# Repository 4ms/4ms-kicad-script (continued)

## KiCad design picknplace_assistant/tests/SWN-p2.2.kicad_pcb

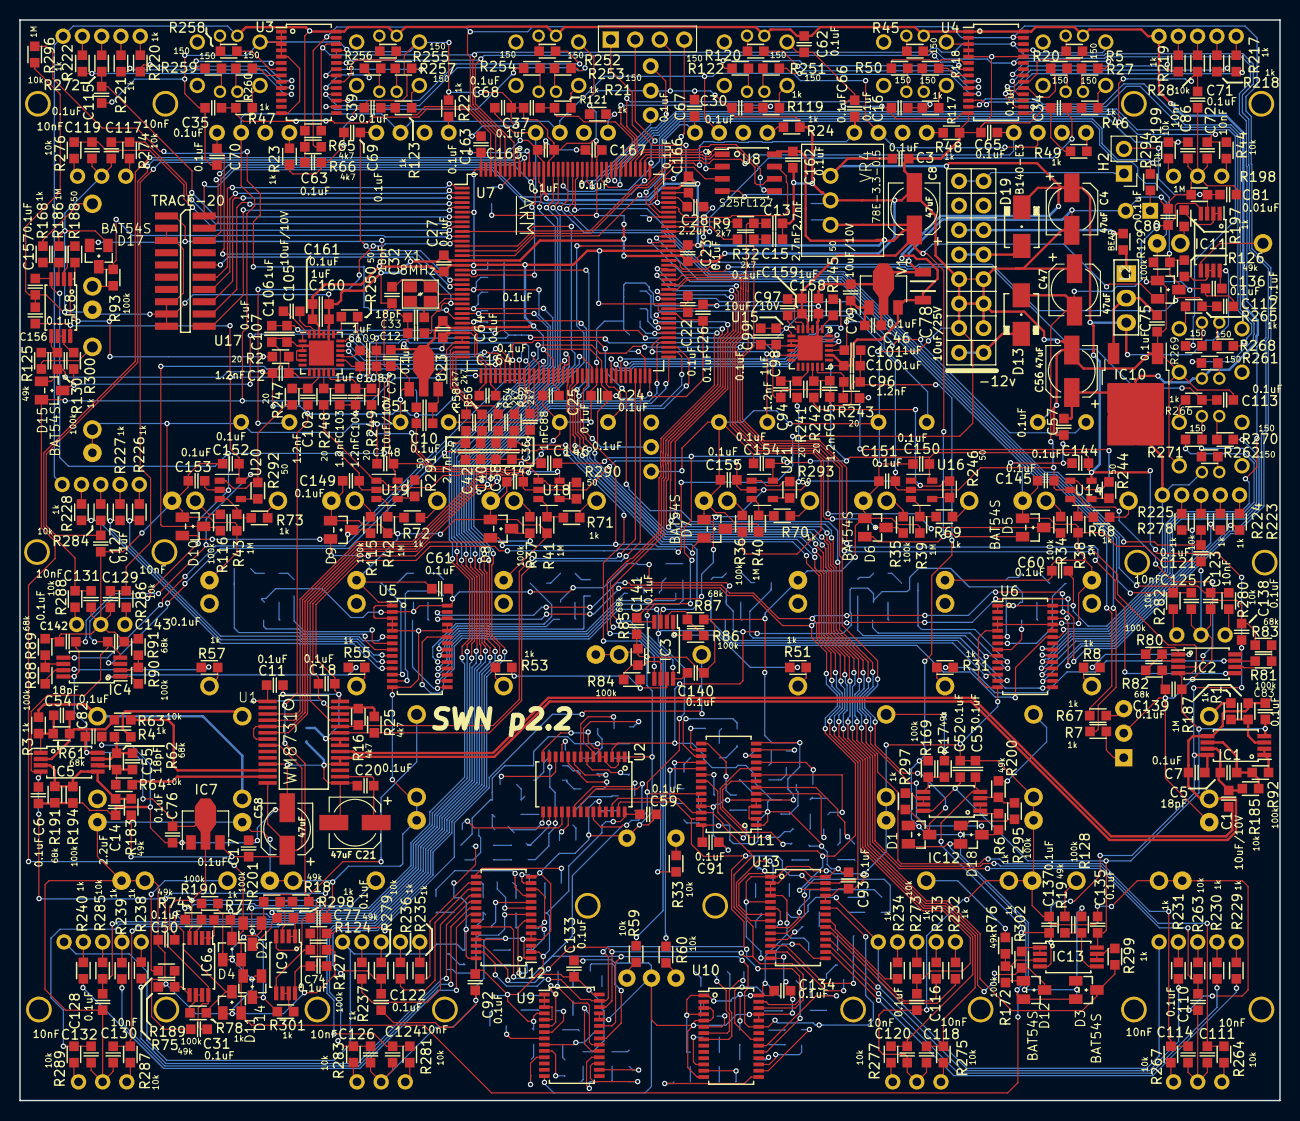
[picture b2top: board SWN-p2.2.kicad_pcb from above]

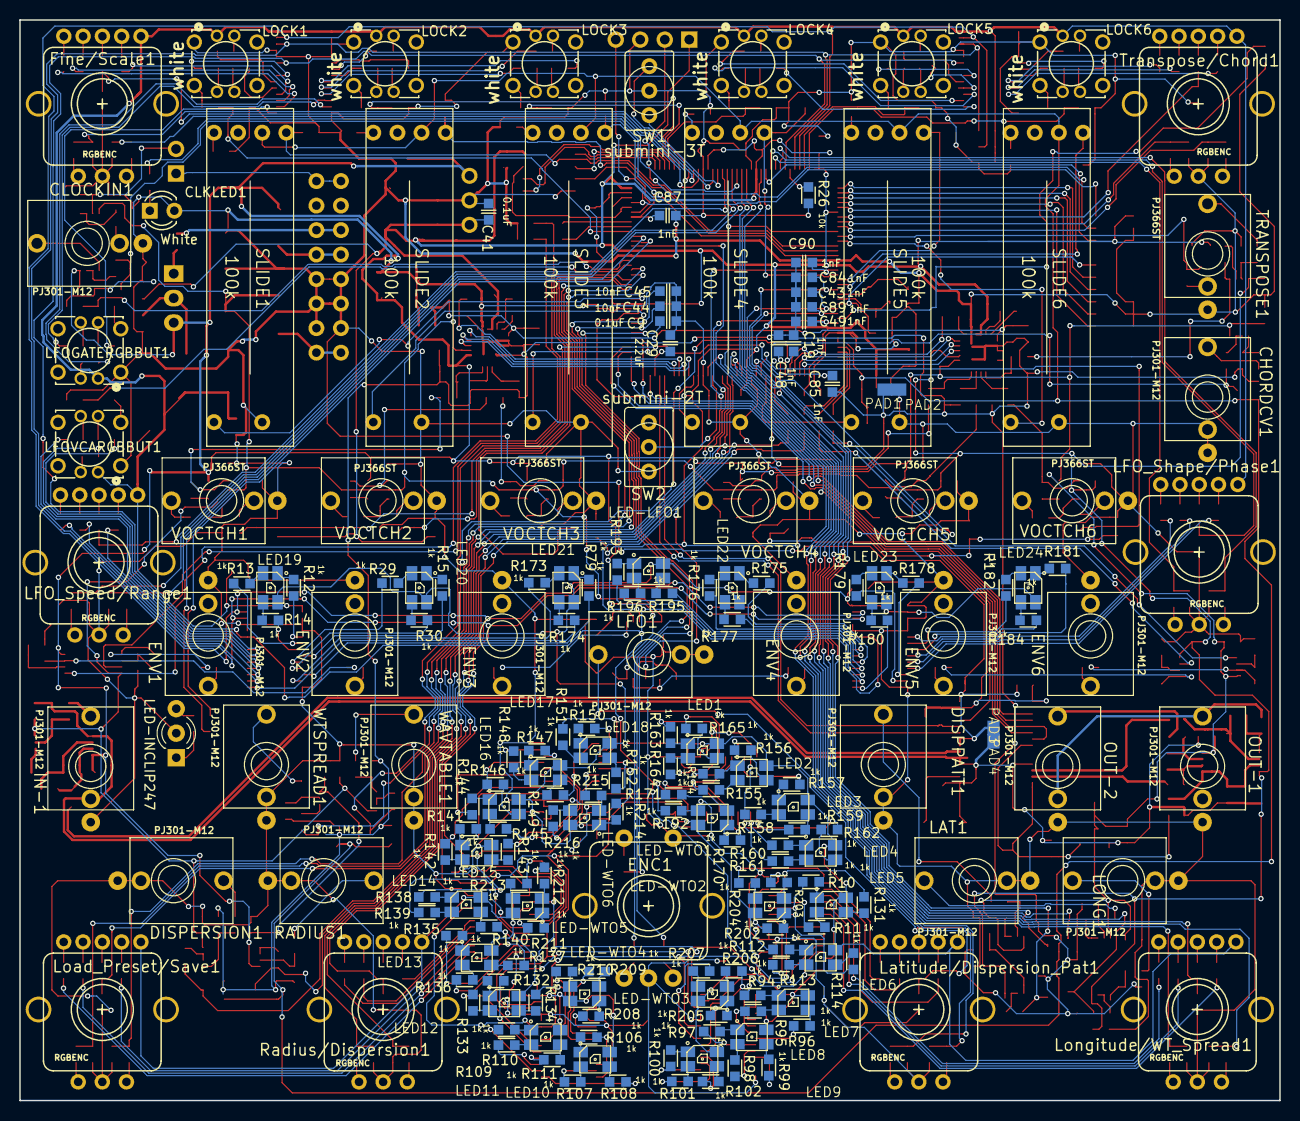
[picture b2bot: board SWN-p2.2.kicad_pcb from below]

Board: 2 copper layers, 130.6 x 112.0 mm, 614 parts (196 on the bottom side), 578 nets.

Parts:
C1, C51, C79, C97, C105: 10uF/10V; C0603
C2, C94, C95, C96, C102, C103, C104: 1.2nF; C0603
C3, C6, C7, C9, C10, C11, C12, C16, C17, C18, C20, C22, C23, C24, C25, C26, C27, C30, C31, C34, C35, C37, C39, C41, C46, C50, C52, C53, C57, C59, C60, C61, C62, C63, C64, C65, C66, C67, C68, C69, C70, C71, C73, C74, C75, C76, C77, C80, C82, C83, C91, C92, C93, C99, C107, C110, C112, C113, C115, C116, C121, C122, C127, C128, C133, C134, C135, C136, C137, C138, C139, C140, C141, C142, C143, C144, C145, C146, C147, C148, C149, C150, C151, C152, C153, C154, C155, C156, C157, C159, C161, C162, C163, C164, C165, C166, C167: 0.1uF; C0603
C4, C8, C21, C47, C56, C58: 47uF; CP_Elec_5x5.3
C5, C32, C33, C54, C55: 18pF; C0603
C13, C15, C36, C38, C40, C42: 2.7nF; C0603
C14, C28, C29: 2.2uF; C0603
C19, C43, C48, C49, C84, C85, C87, C88, C89, C90: 1nF; C0603
C44, C45, C72, C86, C111, C114, C117, C118, C119, C120, C123, C124, C125, C126, C129, C130, C131, C132: 10nF; C0603
C78: 10uF/25V; C1206
C81: 0.01uF; C0603
C98, C100, C101, C106, C108, C109, C158, C160: 1uF; C0603
CHORDCV1: PJ301-M12; PJ301M-12
CLKLED1: White; LED-C1-A2-3MM-VERT
CLOCKIN1: PJ301-M12; PJ301M-12
D1, D2, D3, D4, D5, D6, D7, D8, D9, D10, D11, D12, D14, D15, D16, D17, D18: BAT54S; SOT23
D13, D19: B140-E3; SMA_Standard
DISPERSION1: PJ301-M12; PJ301M-12
DISPPATT1: PJ301-M12; PJ301M-12
ENC1: ROTENC-BUTTON-A; ROTENC-12MM-BUT
ENV1, ENV2, ENV3, ENV4, ENV5, ENV6: PJ301-M12; PJ301M-12
Fine/Scale1: RGBENC; RGB_ROTARY_ENCODER
H1: TRACE-20; CONN-2x10-SMT-127
H2: BUSCLK; Pin_Header_Straight_1x02_Pitch2.54mm
IC1, IC5, IC8: NJM2068; TSSOP-8_4.4x3mm_Pitch0.65mm
IC2, IC3, IC4, IC6, IC9, IC11, IC12, IC13: TL082; TSSOP-8_4.4x3mm_Pitch0.65mm
IC7: MCP1703x-3302E/MB; SOT-89-3
IC10: LD1117ADT33TR; TO-252-2
IN-1: PJ301-M12; PJ301M-12
J1: HEADER-1X3-TH; Pin_Header_Straight_1x03
J2: HEADER-2X8-TH; HEADER-2X8-TH_eagle_pinout
L2: BEAD; R0603
LAT1: PJ301-M12; PJ301M-12
LED1, LED2, LED3, LED4, LED5, LED6, LED7, LED8, LED9, LED10, LED11, LED12, LED13, LED14, LED15, LED16, LED17, LED18, LED19, LED20, LED21, LED22, LED23, LED24: LED-RGB-CA-HEBEI; LED-PLCC4
LED-INCLIP247: LEDX2A; LED_D3.0mm-3
LED-LFO1: LED-RGB-CA-HEBEI; LED-PLCC4
LED-WTO1, LED-WTO2, LED-WTO3, LED-WTO4, LED-WTO5, LED-WTO6: LED-RGB-CA-HEBEI; LED-PLCC4
LFO1: PJ301-M12; PJ301M-12
LFOGATERGBBUT1: SPST-ILLUM-RGB; RGB-SPST-LED-TC002
LFOVCARGBBUT1: SPST-ILLUM-RGB; RGB-SPST-LED-TC002
LFO_Shape/Phase1: RGBENC; RGB_ROTARY_ENCODER
LFO_Speed/Range1: RGBENC; RGB_ROTARY_ENCODER
LOCK1, LOCK2, LOCK3, LOCK4, LOCK5, LOCK6: SPST-ILLUM-RGB; RGB-SPST-LED-TC002
LONG1: PJ301-M12; PJ301M-12
Latitude/Dispersion_Pat1: RGBENC; RGB_ROTARY_ENCODER
Load_Preset/Save1: RGBENC; RGB_ROTARY_ENCODER
Longitude/WT_Spread1: RGBENC; RGB_ROTARY_ENCODER
OUT-1, OUT-2: PJ301-M12; PJ301M-12
PAD1, PAD2, PAD3, PAD4: PAD-06
R1, R3, R4, R6, R7, R8, R10, R11, R12, R13, R14, R15, R21, R22, R23, R24, R29, R30, R31, R46, R47, R48, R49, R51, R53, R55, R57, R67, R68, R69, R70, R71, R72, R73, R77, R78, R79, R94, R95, R96, R97, R98, R99, R100, R101, R102, R106, R107, R108, R109, R110, R111, R112, R113, R114, R117, R119, R121, R123, R131, R132, R133, R134, R135, R136, R137, R138, R139, R140, R141, R142, R143, R144, R145, R146, R147, R148, R149, R150, R151, R152, R154, R155, R156, R157, R158, R159, R160, R161, R162, R163, R164, R165, R168, R170, R171, R173, R174, R175, R176, R177, R178, R179, R180, R181, R182, R184, R192, R193, R195, R196, R197, R202, R203, R204, R205, R206, R207, R208, R209, R210, R211, R212, R213, R214, R215, R216, R217, R218, R219, R220, R221, R222, R223, R224, R225, R226, R227, R228, R229, R230, R231, R232, R233, R234, R235, R236, R237, R238, R239, R240, R265, R266, R297, R298, R299, R300, R301, R302: 1k; R0603
R2, R241, R242, R243, R247, R248, R249: 20; R0603
R5, R20, R27, R45, R50, R118, R120, R122, R251, R252, R253, R254, R255, R256, R257, R258, R259, R260, R261, R262, R268, R269, R270, R271: 150; R0603
R9, R32, R52, R54, R56, R58: 2k7; R0603
R16, R25, R65, R66: 4k7; R0603
R17, R18, R19, R74, R75, R76, R124, R125, R126, R183, R200: 49k; R0603
R26, R28, R33, R44, R59, R60, R63, R64, R185, R199, R263, R264, R267, R272, R273, R274, R275, R276, R277, R278, R279, R280, R281, R282, R283, R284, R285, R286, R287, R288, R289, R294: 10k; R0603
R34, R35, R36, R37, R80, R81, R84, R86, R88, R90, R92, R93, R115, R116, R127, R128, R129, R130, R169, R172, R189, R190, R194, R201, R295: 100k; R0603
R38, R39, R40, R41, R42, R43, R186, R187, R198, R296: 1M; R0603
R61, R62, R82, R83, R85, R87, R89, R91, R191: 68k; R0603
R188, R244, R245, R246, R250, R290, R291, R292, R293: 50; R0603
RADIUS1: PJ301-M12; PJ301M-12
Radius/Dispersion1: RGBENC; RGB_ROTARY_ENCODER
SLIDE1, SLIDE2, SLIDE3, SLIDE4, SLIDE5, SLIDE6: 100k; POT-SLIDER-LED-ALPHA-RA2045F-20
SW1: submini-3T; SPDT-SUB
SW2: submini-2T; SPDT-SUB
SWD_1: HEADER-1X4; Pin_Header_Straight_1x04_Pitch2.54mm
TRANSPOSE1: PJ366ST; PJ301M-12
Transpose/Chord1: RGBENC; RGB_ROTARY_ENCODER
U1: WM8731; SSOP-28
U2, U3, U4, U5, U6, U9, U10, U11, U12, U13: PCA9685; TSSOP-28_4.4x9.7mm_Pitch0.65mm
U7: STM32F427ZG; LQFP-144_ARM_20x20mm_Pitch0.5mm
U8: S25FL127; SOIC-8_3.9x4.9mm_Pitch1.27mm
U14, U16, U18, U19, U20, U21: LM7321; SOT-23-5
U15, U17: ADS8634; QFN-24-1EP_4x4mm_Pitch0.5mm
U23: MCP1703x-3302E/MB; SOT-89-3
V1: KA78L05; SOT-89-3
VOCTCH1, VOCTCH2, VOCTCH3, VOCTCH4, VOCTCH5, VOCTCH6: PJ366ST; PJ301M-12
VR4: 78E-3.3-0.5; RECOM-DCDC
WAVTABLE1: PJ301-M12; PJ301M-12
WTSPREAD1: PJ301-M12; PJ301M-12
X1: 8MHz; FA-238-Pins1and2diag

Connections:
5VEXT: J1.1, L2.2
+3.3V: C8.1, C11.1, C18.1, C22.1, C23.1, C24.1, C25.1, C26.1, C27.1, C41.1, C64.1, C73.1, C158.1, C159.1, C160.1, C161.1, C162.1, C163.1, C164.1, C165.1, C166.1, C167.1, D5.2, D6.2, D7.2, D8.2, D9.2, D10.2, D16.2, D17.2, H1.1, R16.1, R25.1, SWD_1.1, U1.1, U1.27, U7.6, U7.17, U7.30, U7.39, U7.52, U7.62, U7.72, U7.82, U7.84, U7.95, U7.108, U7.121, U7.131, U7.143, U7.144, U8.8, U15.21, U15.22, U17.21, U17.22, U23.2, VR4.3
+5V: C46.2, C79.2, C98.1, C99.1, C106.1, C107.1, U15.1, U17.1, V1.1
+12V: C3.1, C4.1, C7.2, C50.2, C53.2, C76.1, C77.2, C78.1, C82.2, C100.1, C108.1, C136.2, C137.2, C138.2, C140.2, C142.2, C144.1, C146.1, C148.1, C150.1, C152.1, C154.1, C156.1, D19.1, IC1.8, IC2.8, IC3.8, IC4.8, IC5.8, IC6.4, IC7.2, IC8.8, IC9.4, IC11.8, IC12.4, IC13.4, J1.3, U14.5, U15.14, U16.5, U17.14, U18.5, U19.5, U20.5, U21.5, V1.3, VR4.1
-12V: C6.1, C31.1, C47.2, C52.1, C74.1, C80.1, C83.1, C101.1, C109.1, C135.1, C139.2, C141.2, C143.2, C145.1, C147.1, C149.1, C151.1, C153.1, C155.1, C157.1, D13.2, IC1.4, IC2.4, IC3.4, IC4.4, IC5.4, IC6.8, IC8.4, IC9.8, IC11.4, IC12.8, IC13.8, U14.2, U15.15, U16.2, U17.15, U18.2, U19.2, U20.2, U21.2
/V/OCT ADC/TRANSPOSEADC: IC8.1, R2.1, R188.1
/V/OCT ADC/VOLTADC1: R243.1, R244.1, U14.1
/V/OCT ADC/VOLTADC2: R242.1, R246.1, U16.1
/V/OCT ADC/VOLTADC3: R241.1, R293.1, U21.1
/V/OCT ADC/VOLTADC4: R249.1, R290.1, U18.1
/V/OCT ADC/VOLTADC5: R248.1, R291.1, U19.1
/V/OCT ADC/VOLTADC6: R247.1, R292.1, U20.1
ADC-VDD: C10.1, C51.1, D1.2, D2.2, D3.2, D4.2, D11.2, D12.2, D14.2, D15.2, D18.2, SLIDE1.P1, SLIDE2.P1, SLIDE3.P1, SLIDE4.P1, SLIDE5.P1, SLIDE6.P1, U7.32, U7.33, U23.3
AGND: C6.2, C7.1, C14.2, C17.2, C20.2, C21.2, C58.2, C76.2, C82.1, C83.2, IC1.5, IC7.1, IN-1.3, PAD3.1, R187.2, R191.1, R194.1, U1.11, U1.15, U1.18, U1.19
CHORDADC: C88.1, D15.3, R300.2, U7.47
CLKINADC: C87.1, D16.3, R126.2, R129.1, U7.102
CLKLED: R294.1, U7.127
CODEC-VDD: C17.1, C58.1, IC7.3, R183.2, U1.8, U1.14
DISPADC: C90.1, D3.3, R299.2, U7.18
DISPPATADC: C84.1, D2.3, R298.2, U7.22
ENVPWM1: R9.2, U7.101
ENVPWM2: R32.2, U7.100
ENVPWM3: R52.2, U7.46
ENVPWM4: R54.2, U7.36
ENVPWM5: R56.2, U7.35
ENVPWM6: R58.2, U7.34
FINEENC1: C72.1, R44.2, U7.118
FINEENC2: C86.1, R199.1, U7.119
FINESW1: C71.1, R28.2, U7.117
GND: C3.2, C4.2, C8.2, C9.2, C11.2, C12.2, C13.2, C15.2, C16.2, C18.2, C22.2, C23.2, C24.2, C25.2, C26.2, C27.2, C28.2, C29.2, C30.2, C31.2, C32.1, C33.1, C34.2, C35.2, C36.2, C37.2, C38.2, C39.2, C40.2, C41.2, C42.2, C44.2, C45.2, C46.1, C47.1, C50.1, C52.2, C53.1, C56.2, C57.2, C59.2, C60.2, C61.2, C62.2, C63.2, C64.2, C65.2, C66.2, C67.2, C68.2, C69.2, C70.2, C71.2, C72.2, C73.2, C74.2, C75.2, C77.1, C78.2, C79.1, C80.2, C81.2, C86.2, C87.2, C91.2, C92.2, C93.2, C110.2, C111.2, C112.2, C113.2, C114.2, C115.2, C116.2, C117.2, C118.2, C119.2, C120.2, C121.2, C122.2, C123.2, C124.2, C125.2, C126.2, C127.2, C128.2, C129.2, C130.2, C131.2, C132.2, C133.2, C134.2, C135.2, C136.1, C137.1, C138.1, C139.1, C140.1, C141.1, C142.1, C143.1, C144.2, C145.2, C146.2, C147.2, C148.2, C149.2, C150.2, C151.2, C152.2, C153.2, C154.2, C155.2, C156.2, C157.2, C158.2, C159.2, C160.2, C161.2, C162.2, C163.2, C164.2, C165.2, C166.2, C167.2, CHORDCV1.2, CHORDCV1.3, CLKLED1.1, CLOCKIN1.2, D5.1, D6.1, D7.1, D8.1, D9.1, D10.1, D16.1, D17.1, DISPERSION1.2, DISPERSION1.3, DISPPATT1.2, DISPPATT1.3, ENC1.2, ENC1.SW2, ENV1.2, ENV2.2, ENV3.2, ENV4.2, ENV5.2, ENV6.2, Fine/Scale1.2, H1.3, H1.5, H1.15, H1.17, H1.19, IC10.1, IN-1.2, J2.3, J2.4, J2.5, J2.6, J2.7, J2.8, LAT1.2, LAT1.3, LED-INCLIP247.2, LFO1.2, LFO1.3, LFOGATERGBBUT1.1, LFOVCARGBBUT1.1, LFO_Shape/Phase1.2, LFO_Speed/Range1.2, LOCK1.1, LOCK2.1, LOCK3.1, LOCK4.1, LOCK5.1, LOCK6.1, LONG1.2, LONG1.3, Latitude/Dispersion_Pat1.2, Load_Preset/Save1.2, Longitude/WT_Spread1.2, OUT-1.2, OUT-2.2, PAD2.1, PAD4.1, R21.2, R22.2, R23.2, R24.2, R26.2, R38.2, R39.2, R40.2, R41.2, R42.2, R43.2, R48.2, R49.2, R82.2, R83.2, R85.2, R87.2, R89.2, R91.2, R129.2, R186.2, R198.2, R296.1, RADIUS1.2, RADIUS1.3, Radius/Dispersion1.2, SLIDE1.P3, SLIDE2.P3, SLIDE3.P3, SLIDE4.P3, SLIDE5.P3, SLIDE6.P3, SW1.2, SW2.1, SWD_1.3, TRANSPOSE1.2, Transpose/Chord1.2, U1.21, U1.22, U1.28, U2.1, U2.2, U2.4, U2.5, U2.14, U2.24, U2.25, U3.1, U3.2, U3.3, U3.4, U3.5, U3.14, U3.24, U3.25, U4.2, U4.3, U4.4, U4.5, U4.14, U4.24, U4.25, U5.1, U5.3, U5.4, U5.5, U5.14, U5.24, U5.25, U6.3, U6.4, U6.5, U6.14, U6.24, U6.25, U7.16, U7.31, U7.38, U7.51, U7.61, U7.83, U7.94, U7.107, U7.120, U7.130, U8.4, U9.14, U9.24, U9.25, U10.2, U10.3, U10.5, U10.14, U10.24, U10.25, U11.2, U11.4, U11.5, U11.14, U11.24, U11.25, U12.1, U12.4, U12.5, U12.14, U12.24, U12.25, U13.1, U13.5, U13.14, U13.24, U13.25, U15.20, U17.20, U23.1, V1.2, VOCTCH1.2, VOCTCH2.2, VOCTCH3.2, VOCTCH4.2, VOCTCH5.2, VOCTCH6.2, VR4.2, WAVTABLE1.2, WAVTABLE1.3, WTSPREAD1.2, WTSPREAD1.3
GNDADC: C2.2, C10.2, C19.2, C43.2, C48.2, C49.2, C51.2, C84.2, C85.2, C88.2, C89.2, C90.2, C94.2, C95.2, C96.2, C98.2, C99.2, C100.2, C101.2, C102.2, C103.2, C104.2, C106.2, C107.2, C108.2, C109.2, D1.1, D2.1, D3.1, D4.1, D11.1, D12.1, D14.1, D15.1, D18.1, PAD1.1, R127.2, R128.2, R130.2, R169.2, R172.2, R189.2, R190.2, R201.2, R295.2, U15.2, U15.3, U15.5, U15.25, U17.2, U17.3, U17.5, U17.25
I2C1_SCL: R65.2, U2.26, U3.26, U4.26, U5.26, U6.26, U7.139, U9.26, U10.26, U11.26, U12.26, U13.26
I2C1_SDA: R66.2, U2.27, U3.27, U4.27, U5.27, U6.27, U7.140, U9.27, U10.27, U11.27, U12.27, U13.27
I2C2_SCL: R16.2, U1.24, U7.69
I2C2_SDA: R25.2, U1.23, U7.70
I2S2_LRCK: U1.5, U1.7, U7.73
I2S2_MCLK: U1.25, U7.96
I2S2_SCLK: U1.3, U7.74
I2S2_SDI: U1.6, U7.75
I2S2_SDO: U1.4, U7.76
IN-CLIP-L: R7.2, U7.98
IN-CLIP-R: R67.1, U7.97
IN-L: C1.1, U1.20
KEYS: SW1.1, U7.123
LATADC: C43.1, D4.3, R77.2, U7.26
LATITUDEENC1: C124.1, R281.2, U7.53
LATITUDEENC2: C126.1, R283.1, U7.54
LATITUDESW1: C122.1, R279.2, U7.10
LEDRING_OE: U2.23, U3.23, U4.23, U5.23, U6.23, U7.137, U9.23, U10.23, U11.23, U12.23, U13.23
LEDRING_VCC: C56.1, C57.1, C59.1, C60.1, C61.1, C62.1, C63.1, C91.1, C92.1, C93.1, C133.1, C134.1, Fine/Scale1.8, IC10.2, LED1.2, LED2.2, LED3.2, LED4.2, LED5.2, LED6.2, LED7.2, LED8.2, LED9.2, LED10.2, LED11.2, LED12.2, LED13.2, LED14.2, LED15.2, LED16.2, LED17.2, LED18.2, LED19.2, LED20.2, LED21.2, LED22.2, LED23.2, LED24.2, LED-LFO1.2, LED-WTO1.2, LED-WTO2.2, LED-WTO3.2, LED-WTO4.2, LED-WTO5.2, LED-WTO6.2, LFOGATERGBBUT1.5, LFOVCARGBBUT1.5, LFO_Shape/Phase1.8, LFO_Speed/Range1.8, LOCK1.5, LOCK2.5, LOCK3.5, LOCK4.5, LOCK5.5, LOCK6.5, Latitude/Dispersion_Pat1.8, Load_Preset/Save1.8, Longitude/WT_Spread1.8, R65.1, R66.1, Radius/Dispersion1.8, Transpose/Chord1.8, U2.3, U2.28, U3.28, U4.1, U4.28, U5.2, U5.28, U6.1, U6.2, U6.28, U9.4, U9.28, U10.1, U10.4, U10.28, U11.1, U11.3, U11.28, U12.2, U12.3, U12.28, U13.2, U13.3, U13.4, U13.28
LFOADC: C89.1, D14.3, R301.2, U7.27
LFOGATEBUT: C112.1, R265.1, U7.93
LFOGATE_B: R269.1, U4.15
LFOGATE_G: R261.2, U4.13
LFOGATE_R: R268.1, U4.12
LFOSHAPEENC1: C129.1, R286.2, U7.135
LFOSHAPEENC2: C131.1, R288.1, U7.136
LFOSHAPESW1: C127.1, R284.2, U7.134
LFOSPEEDENC1: C123.1, R280.2, U7.125
LFOSPEEDENC2: C125.1, R282.1, U7.126
LFOSPEEDSW1: C121.1, R278.2, U7.124
LFOVCABUT: C113.1, R266.1, U7.92
LFOVCA_B: R271.1, U6.21
LFOVCA_G: R262.2, U6.20
LFOVCA_R: R270.1, U6.19
LOCK1_B: R27.1, U4.21
LOCK1_G: R5.2, U4.20
LOCK1_R: R20.1, U4.19
LOCK2_B: R118.1, U4.8
LOCK2_G: R45.2, U4.7
LOCK2_R: R50.1, U4.6
LOCK3_B: R251.1, U4.11
LOCK3_G: R120.2, U4.10
LOCK3_R: R122.1, U4.9
LOCK4_B: R254.1, U3.18
LOCK4_G: R252.2, U3.17
LOCK4_R: R253.1, U3.16
LOCK5_B: R257.1, U3.21
LOCK5_G: R255.2, U3.20
LOCK5_R: R256.1, U3.19
LOCK6_B: R260.1, U3.8
LOCK6_G: R258.2, U3.7
LOCK6_R: R259.1, U3.6
LOCKBUT1: C34.1, R46.1, U7.99
LOCKBUT2: C16.1, R117.1, U7.114
LOCKBUT3: C30.1, R119.1, U7.115
LOCKBUT4: C37.1, R121.1, U7.116
LOCKBUT5: C39.1, R123.1, U7.141
LOCKBUT6: C35.1, R47.1, U7.142
LONGADC: C48.1, D11.3, R78.2, U7.45
LONGITUDEENC1: C130.1, R287.2, U7.128
LONGITUDEENC2: C132.1, R289.1, U7.129
LONGITUDESW1: C128.1, R285.2, U7.132
MUTES: SW1.3, U7.122
NRST: C12.1, H1.10, U7.25
unnamed: C1.2, C5.1, IC1.7, R185.2
unnamed: C2.1, R2.2, U17.8
unnamed: C5.2, IC1.6, R92.2, R185.1
unnamed: C13.1, IC2.3, R9.1
unnamed: C14.1, IC5.3, IC5.5, R183.1, R191.2, R194.2
unnamed: C15.1, IC2.5, R32.1
unnamed: C20.1, C21.1, U1.16
unnamed: C28.1, U7.106
unnamed: C29.1, U7.71
unnamed: C32.2, U7.23, X1.1
unnamed: C33.2, U7.24, X1.2
unnamed: C36.1, IC3.3, R52.1
unnamed: C38.1, IC3.5, R54.1
unnamed: C40.1, IC4.3, R56.1
unnamed: C42.1, IC4.5, R58.1
unnamed: C54.1, IC5.1, R3.2, R61.2
unnamed: C54.2, IC5.2, R61.1, R63.2
unnamed: C55.1, IC5.7, R4.2, R62.2
unnamed: C55.2, IC5.6, R62.1, R64.2
unnamed: C75.1, IC10.3, J1.2
unnamed: C94.1, R241.2, U15.9
unnamed: C95.1, R242.2, U15.10
unnamed: C96.1, R243.2, U15.11
unnamed: C97.1, U15.24
unnamed: C97.2, U15.23
unnamed: C102.1, R247.2, U17.9
unnamed: C103.1, R248.2, U17.10
unnamed: C104.1, R249.2, U17.11
unnamed: C105.1, U17.24
unnamed: C105.2, U17.23
unnamed: CHORDCV1.1, R125.1
unnamed: CLKLED1.2, R294.2
unnamed: CLOCKIN1.1, IC11.5
unnamed: CLOCKIN1.3, R197.1
unnamed: D13.1, J2.1, J2.2
unnamed: D19.2, J2.9, J2.10
unnamed: DISPERSION1.1, R19.1
unnamed: DISPPATT1.1, R18.1
unnamed: ENC1.1, R60.2
unnamed: ENC1.3, R59.1
unnamed: ENC1.SW1, R33.1
unnamed: ENV1.1, R8.1
unnamed: ENV2.1, R31.1
unnamed: ENV3.1, R51.1
unnamed: ENV4.1, R53.1
unnamed: ENV5.1, R55.1
unnamed: ENV6.1, R57.1
unnamed: Fine/Scale1.1, R44.1
unnamed: Fine/Scale1.3, R199.2
unnamed: Fine/Scale1.4, R217.2
unnamed: Fine/Scale1.5, R218.2
unnamed: Fine/Scale1.6, R28.1
unnamed: Fine/Scale1.7, R219.2
unnamed: H2.1, J2.15, J2.16
unnamed: IC1.1, IC1.2, R92.1
unnamed: IC1.3, R1.2, R187.1
unnamed: IC2.1, R8.2, R80.1
unnamed: IC2.2, R80.2, R82.1
unnamed: IC2.6, R81.2, R83.1
unnamed: IC2.7, R31.2, R81.1
unnamed: IC3.1, R51.2, R86.1
unnamed: IC3.2, R86.2, R87.1
unnamed: IC3.6, R84.2, R85.1
unnamed: IC3.7, R53.2, R84.1
unnamed: IC4.1, R55.2, R90.1
unnamed: IC4.2, R90.2, R91.1
unnamed: IC4.6, R88.2, R89.1
unnamed: IC4.7, R57.2, R88.1
unnamed: IC6.1, IC6.2, R77.1
unnamed: IC6.3, R74.2, R190.1
unnamed: IC6.5, R75.2, R189.1
unnamed: IC6.6, IC6.7, R78.1
unnamed: IC8.2, R188.2
unnamed: IC8.3, R168.1, R186.1
unnamed: IC8.5, R125.2, R130.1
unnamed: IC8.6, IC8.7, R300.1
unnamed: IC9.1, IC9.2, R298.1
unnamed: IC9.3, R18.2, R201.1
unnamed: IC9.5, R124.2, R127.1
unnamed: IC9.6, IC9.7, R301.1
unnamed: IC11.1, IC11.2, R197.2
unnamed: IC11.6, IC11.7, R126.1
unnamed: IC12.1, IC12.2, R6.1
unnamed: IC12.3, R200.2, R295.1
unnamed: IC12.5, R17.2, R169.1
unnamed: IC12.6, IC12.7, R297.1
unnamed: IC13.1, IC13.2, R302.1
unnamed: IC13.3, R76.2, R172.1
unnamed: IC13.5, R19.2, R128.1
unnamed: IC13.6, IC13.7, R299.1
unnamed: IN-1.1, R1.1
unnamed: J2.11, J2.12, L2.1
unnamed: LAT1.1, R74.1
unnamed: LED1.1, R163.2
unnamed: LED1.3, R165.2
unnamed: LED1.4, R164.2
unnamed: LED2.1, R154.2
unnamed: LED2.3, R156.2
unnamed: LED2.4, R155.2
unnamed: LED3.1, R157.2
unnamed: LED3.3, R159.2
unnamed: LED3.4, R158.2
unnamed: LED4.1, R160.2
unnamed: LED4.3, R162.2
unnamed: LED4.4, R161.2
unnamed: LED5.1, R10.2
unnamed: LED5.3, R131.2
unnamed: LED5.4, R11.2
unnamed: LED6.1, R112.2
unnamed: LED6.3, R114.2
unnamed: LED6.4, R113.2
unnamed: LED7.1, R94.2
unnamed: LED7.3, R96.2
unnamed: LED7.4, R95.2
unnamed: LED8.1, R97.2
unnamed: LED8.3, R99.2
unnamed: LED8.4, R98.2
unnamed: LED9.1, R100.2
unnamed: LED9.3, R102.2
unnamed: LED9.4, R101.2
unnamed: LED10.1, R106.2
unnamed: LED10.3, R108.2
unnamed: LED10.4, R107.2
unnamed: LED11.1, R109.2
unnamed: LED11.3, R111.2
unnamed: LED11.4, R110.2
unnamed: LED12.1, R132.2
unnamed: LED12.3, R134.2
unnamed: LED12.4, R133.2
unnamed: LED13.1, R135.2
unnamed: LED13.3, R137.2
unnamed: LED13.4, R136.2
unnamed: LED14.1, R138.2
unnamed: LED14.3, R140.2
unnamed: LED14.4, R139.2
unnamed: LED15.1, R141.2
unnamed: LED15.3, R143.2
unnamed: LED15.4, R142.2
unnamed: LED16.1, R144.2
unnamed: LED16.3, R146.2
unnamed: LED16.4, R145.2
unnamed: LED17.1, R147.2
unnamed: LED17.3, R149.2
unnamed: LED17.4, R148.2
unnamed: LED18.1, R150.2
unnamed: LED18.3, R152.2
unnamed: LED18.4, R151.2
unnamed: LED19.1, R12.2
unnamed: LED19.3, R14.2
unnamed: LED19.4, R13.2
unnamed: LED20.1, R15.2
unnamed: LED20.3, R30.2
unnamed: LED20.4, R29.2
unnamed: LED21.1, R79.2
unnamed: LED21.3, R174.2
unnamed: LED21.4, R173.2
unnamed: LED22.1, R175.2
unnamed: LED22.3, R177.2
unnamed: LED22.4, R176.2
unnamed: LED23.1, R178.2
unnamed: LED23.3, R180.2
unnamed: LED23.4, R179.2
unnamed: LED24.1, R181.2
unnamed: LED24.3, R184.2
unnamed: LED24.4, R182.2
unnamed: LED-INCLIP247.1, R7.1
unnamed: LED-INCLIP247.3, R67.2
unnamed: LED-LFO1.1, R193.2
unnamed: LED-LFO1.3, R196.2
unnamed: LED-LFO1.4, R195.2
unnamed: LED-WTO1.1, R170.2
unnamed: LED-WTO1.3, R192.2
unnamed: LED-WTO1.4, R171.2
unnamed: LED-WTO2.1, R202.2
unnamed: LED-WTO2.3, R204.2
unnamed: LED-WTO2.4, R203.2
unnamed: LED-WTO3.1, R205.2
unnamed: LED-WTO3.3, R207.2
unnamed: LED-WTO3.4, R206.2
unnamed: LED-WTO4.1, R208.2
unnamed: LED-WTO4.3, R210.2
unnamed: LED-WTO4.4, R209.2
unnamed: LED-WTO5.1, R211.2
unnamed: LED-WTO5.3, R213.2
unnamed: LED-WTO5.4, R212.2
unnamed: LED-WTO6.1, R214.2
unnamed: LED-WTO6.3, R216.2
unnamed: LED-WTO6.4, R215.2
unnamed: LFO1.1, R124.1
unnamed: LFOGATERGBBUT1.3, R265.2
unnamed: LFOGATERGBBUT1.6, R261.1
unnamed: LFOGATERGBBUT1.7, R268.2
unnamed: LFOGATERGBBUT1.8, R269.2
unnamed: LFOVCARGBBUT1.3, R266.2
unnamed: LFOVCARGBBUT1.6, R262.1
unnamed: LFOVCARGBBUT1.7, R270.2
unnamed: LFOVCARGBBUT1.8, R271.2
unnamed: LFO_Shape/Phase1.1, R286.1
unnamed: LFO_Shape/Phase1.3, R288.2
unnamed: LFO_Shape/Phase1.4, R226.2
unnamed: LFO_Shape/Phase1.5, R227.2
unnamed: LFO_Shape/Phase1.6, R284.1
unnamed: LFO_Shape/Phase1.7, R228.2
unnamed: LFO_Speed/Range1.1, R280.1
unnamed: LFO_Speed/Range1.3, R282.2
unnamed: LFO_Speed/Range1.4, R223.2
unnamed: LFO_Speed/Range1.5, R224.2
unnamed: LFO_Speed/Range1.6, R278.1
unnamed: LFO_Speed/Range1.7, R225.2
unnamed: LOCK1.3, R46.2
unnamed: LOCK1.6, R5.1
unnamed: LOCK1.7, R20.2
unnamed: LOCK1.8, R27.2
unnamed: LOCK2.3, R117.2
unnamed: LOCK2.6, R45.1
unnamed: LOCK2.7, R50.2
unnamed: LOCK2.8, R118.2
unnamed: LOCK3.3, R119.2
unnamed: LOCK3.6, R120.1
unnamed: LOCK3.7, R122.2
unnamed: LOCK3.8, R251.2
unnamed: LOCK4.3, R121.2
unnamed: LOCK4.6, R252.1
unnamed: LOCK4.7, R253.2
unnamed: LOCK4.8, R254.2
unnamed: LOCK5.3, R123.2
unnamed: LOCK5.6, R255.1
unnamed: LOCK5.7, R256.2
unnamed: LOCK5.8, R257.2
unnamed: LOCK6.3, R47.2
unnamed: LOCK6.6, R258.1
unnamed: LOCK6.7, R259.2
unnamed: LOCK6.8, R260.2
unnamed: LONG1.1, R75.1
unnamed: Latitude/Dispersion_Pat1.1, R281.1
unnamed: Latitude/Dispersion_Pat1.3, R283.2
unnamed: Latitude/Dispersion_Pat1.4, R235.2
unnamed: Latitude/Dispersion_Pat1.5, R236.2
unnamed: Latitude/Dispersion_Pat1.6, R279.1
unnamed: Latitude/Dispersion_Pat1.7, R237.2
unnamed: Load_Preset/Save1.1, R264.1
unnamed: Load_Preset/Save1.3, R267.2
unnamed: Load_Preset/Save1.4, R229.2
unnamed: Load_Preset/Save1.5, R230.2
unnamed: Load_Preset/Save1.6, R263.1
unnamed: Load_Preset/Save1.7, R231.2
unnamed: Longitude/WT_Spread1.1, R287.1
unnamed: Longitude/WT_Spread1.3, R289.2
unnamed: Longitude/WT_Spread1.4, R238.2
unnamed: Longitude/WT_Spread1.5, R239.2
unnamed: Longitude/WT_Spread1.6, R285.1
unnamed: Longitude/WT_Spread1.7, R240.2
unnamed: OUT-1.1, OUT-2.3, R3.1
unnamed: OUT-2.1, R4.1
unnamed: R10.1, U12.9
unnamed: R11.1, U12.10
unnamed: R12.1, U6.6
unnamed: R13.1, U6.7
unnamed: R14.1, U6.8
unnamed: R15.1, U6.9
unnamed: R17.1, WAVTABLE1.1
unnamed: R21.1, SLIDE4.LEDC
unnamed: R22.1, SLIDE5.LEDC
unnamed: R23.1, SLIDE6.LEDC
unnamed: R24.1, SLIDE3.LEDC
unnamed: R26.1, U7.138
unnamed: R29.1, U6.10
unnamed: R30.1, U6.11
unnamed: R34.2, VOCTCH1.3
unnamed: R35.1, VOCTCH2.3
unnamed: R36.1, VOCTCH3.3
unnamed: R37.2, VOCTCH4.3
unnamed: R38.1, R68.1, U14.3
unnamed: R39.1, R69.1, U16.3
unnamed: R40.1, R70.1, U21.3
unnamed: R41.1, R71.1, U18.3
unnamed: R42.1, R72.1, U19.3
unnamed: R43.1, R73.1, U20.3
unnamed: R48.1, SLIDE2.LEDC
unnamed: R49.1, SLIDE1.LEDC
unnamed: R68.2, VOCTCH1.1
unnamed: R69.2, VOCTCH2.1
unnamed: R70.2, VOCTCH3.1
unnamed: R71.2, VOCTCH4.1
unnamed: R72.2, VOCTCH5.1
unnamed: R73.2, VOCTCH6.1
unnamed: R76.1, RADIUS1.1
unnamed: R79.1, U6.12
unnamed: R93.2, TRANSPOSE1.3
unnamed: R94.1, U9.6
unnamed: R95.1, U9.7
unnamed: R96.1, U9.8
unnamed: R97.1, U9.9
unnamed: R98.1, U9.10
unnamed: R99.1, U9.11
unnamed: R100.1, U9.16
unnamed: R101.1, U9.17
unnamed: R102.1, U9.18
unnamed: R106.1, U10.12
unnamed: R107.1, U10.13
unnamed: R108.1, U10.15
unnamed: R109.1, U10.16
unnamed: R110.1, U10.17
unnamed: R111.1, U10.18
unnamed: R112.1, U12.6
unnamed: R113.1, U12.7
unnamed: R114.1, U12.8
unnamed: R115.2, VOCTCH5.3
unnamed: R116.2, VOCTCH6.3
unnamed: R131.1, U12.11
unnamed: R132.1, U10.19
unnamed: R133.1, U10.20
unnamed: R134.1, U10.21
unnamed: R135.1, U13.12
unnamed: R136.1, U13.13
unnamed: R137.1, U13.15
unnamed: R138.1, U13.9
unnamed: R139.1, U13.10
unnamed: R140.1, U13.11
unnamed: R141.1, U11.6
unnamed: R142.1, U11.7
unnamed: R143.1, U11.8
unnamed: R144.1, U11.9
unnamed: R145.1, U11.10
unnamed: R146.1, U11.11
unnamed: R147.1, U11.12
unnamed: R148.1, U11.13
unnamed: R149.1, U11.15
unnamed: R150.1, U11.16
unnamed: R151.1, U11.17
unnamed: R152.1, U11.18
unnamed: R154.1, U2.9
unnamed: R155.1, U2.10
unnamed: R156.1, U2.11
unnamed: R157.1, U2.12
unnamed: R158.1, U2.13
unnamed: R159.1, U2.15
unnamed: R160.1, U2.16
unnamed: R161.1, U2.17
unnamed: R162.1, U2.18
unnamed: R163.1, U2.6
unnamed: R164.1, U2.7
unnamed: R165.1, U2.8
unnamed: R168.2, TRANSPOSE1.1
unnamed: R170.1, U2.19
unnamed: R171.1, U2.20
unnamed: R173.1, U6.13
unnamed: R174.1, U6.15
unnamed: R175.1, U5.19
unnamed: R176.1, U5.20
unnamed: R177.1, U5.21
unnamed: R178.1, U5.12
unnamed: R179.1, U5.13
unnamed: R180.1, U5.15
unnamed: R181.1, U5.6
unnamed: R182.1, U5.7
unnamed: R184.1, U5.8
unnamed: R192.1, U2.21
unnamed: R193.1, U5.16
unnamed: R195.1, U5.17
unnamed: R196.1, U5.18
unnamed: R200.1, WTSPREAD1.1
unnamed: R202.1, U12.12
unnamed: R203.1, U12.13
unnamed: R204.1, U12.15
unnamed: R205.1, U9.19
unnamed: R206.1, U9.20
unnamed: R207.1, U9.21
unnamed: R208.1, U10.6
unnamed: R209.1, U10.7
unnamed: R210.1, U10.8
unnamed: R211.1, U13.6
unnamed: R212.1, U13.7
unnamed: R213.1, U13.8
unnamed: R214.1, U11.19
unnamed: R215.1, U11.20
unnamed: R216.1, U11.21
unnamed: R217.1, U4.16
unnamed: R218.1, U4.17
unnamed: R219.1, U4.18
unnamed: R220.1, U3.9
unnamed: R220.2, Transpose/Chord1.4
unnamed: R221.1, U3.10
unnamed: R221.2, Transpose/Chord1.5
unnamed: R222.1, U3.11
unnamed: R222.2, Transpose/Chord1.7
unnamed: R223.1, U6.16
unnamed: R224.1, U6.17
unnamed: R225.1, U6.18
unnamed: R226.1, U5.9
unnamed: R227.1, U5.10
unnamed: R228.1, U5.11
unnamed: R229.1, U13.16
unnamed: R230.1, U13.17
unnamed: R231.1, U13.18
unnamed: R232.1, U13.19
unnamed: R232.2, Radius/Dispersion1.4
unnamed: R233.1, U13.20
unnamed: R233.2, Radius/Dispersion1.5
unnamed: R234.1, U13.21
unnamed: R234.2, Radius/Dispersion1.7
unnamed: R235.1, U12.16
unnamed: R236.1, U12.17
unnamed: R237.1, U12.18
unnamed: R238.1, U12.19
unnamed: R239.1, U12.20
unnamed: R240.1, U12.21
unnamed: R244.2, U14.4
unnamed: R245.1, U15.19
unnamed: R246.2, U16.4
unnamed: R250.1, U17.19
unnamed: R272.1, Transpose/Chord1.6
unnamed: R273.1, Radius/Dispersion1.6
unnamed: R274.1, Transpose/Chord1.1
unnamed: R275.1, Radius/Dispersion1.1
unnamed: R276.2, Transpose/Chord1.3
unnamed: R277.2, Radius/Dispersion1.3
unnamed: R290.2, U18.4
unnamed: R291.2, U19.4
unnamed: R292.2, U20.4
unnamed: R293.2, U21.4
unnamed: R296.2, U7.28
unnamed: U9.1, U9.2, U9.3, U9.5
OUT-L: R63.1, U1.12
OUT-R: R64.1, U1.13
POWERHEADERCLK: C81.1, H2.2, IC11.3, R198.1
PRESETENC1: C111.1, R264.2, U7.90
PRESETENC2: C114.1, R267.1, U7.91
PRESETSW1: C110.1, R263.2, U7.86
RADIUSADC: C49.1, D12.3, R302.2, U7.29
RADIUSENC1: C118.1, R275.2, U7.56
RADIUSENC2: C120.1, R277.1, U7.57
RADIUSSW1: C116.1, R273.2, U7.55
ROTENC1: C44.1, R59.2, U7.79
ROTENC2: C45.1, R60.1, U7.80
ROTENCSW: C9.1, R33.2, U7.78
SENSECH1: D5.3, R34.1, U7.89
SENSECH2: D6.3, R35.2, U7.88
SENSECH3: D7.3, R36.2, U7.87
SENSECH4: D8.3, R37.1, U7.60
SENSECH5: D9.3, R115.1, U7.50
SENSECH6: D10.3, R116.1, U7.49
SENSEXP: D17.3, R93.1, U7.11
SLDADC1: C65.1, SLIDE1.P2, U7.13
SLDADC2: C66.1, SLIDE2.P2, U7.14
SLDADC3: C67.1, SLIDE3.P2, U7.15
SLDADC4: C68.1, SLIDE4.P2, U7.19
SLDADC5: C69.1, SLIDE5.P2, U7.20
SLDADC6: C70.1, SLIDE6.P2, U7.21
SLLED1: SLIDE1.LEDA, U7.85
SLLED2: SLIDE2.LEDA, U7.81
SLLED3: SLIDE3.LEDA, U7.77
SLLED4: SLIDE4.LEDA, U7.63
SLLED5: SLIDE5.LEDA, U7.48
SLLED6: SLIDE6.LEDA, U7.12
SPIADC1_CS: U7.64, U15.16
SPIADC1_DIN: U7.67, U15.18
SPIADC1_DOUT: R245.2, U7.66
SPIADC1_SCLK: U7.65, U15.17
SPIADC2_CS: U7.40, U17.16
SPIADC2_DIN: U7.43, U17.18
SPIADC2_DOUT: R250.2, U7.42
SPIADC2_SCLK: U7.41, U17.17
SPIRAM_CS: U7.110, U8.1
SPIRAM_DIN: U7.113, U8.5
SPIRAM_DOUT: U7.112, U8.2
SPIRAM_IO2: U7.103, U8.3
SPIRAM_IO3: U7.104, U8.7
SPIRAM_SCLK: U7.111, U8.6
SWCK: H1.4, SWD_1.2, U7.109
SWDIO: H1.2, SWD_1.4, U7.105
SWO: H1.6, U7.133
TRACECK: H1.12, U7.1
TRACED0: H1.14, U7.2
TRACED1: H1.16, U7.3
TRACED2: H1.18, U7.4
TRACED3: H1.20, U7.5
TRANSPOSEENC1: C117.1, R274.2, U7.8
TRANSPOSEENC2: C119.1, R276.1, U7.9
TRANSPOSESW1: C115.1, R272.2, U7.7
VOLTOCT_VCA: SW2.2, U7.59
WTADC: C85.1, D1.3, R297.2, U7.37
WTSPREADADC: C19.1, D18.3, R6.2, U7.44

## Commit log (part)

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2017-12-12 picknplace script
2017-12-16 Moved files around in directory, no changes
2017-12-16 Made text wrap, and added debug mode
2018-01-09 Working on faceplate script
2018-01-10 Make faceplate: boundbox.py works, starting removetracks.py
2018-01-12 WIP make faceplate (zones)
2018-01-15 Makefp: copper pour is solid
2018-03-16 experimental auto-find the library name
2018-03-16 Got scripts to work, at least for RCD-FACEPLATE
2018-03-17 Added Zach's paths for each script. Added placeholder for Darcy's script
2018-03-19 deletefootprints.py: Commented out lines 135-137
2018-04-13 Added metal collar 9mm pot
2018-04-13 Added gerbv scripts
    To make a file executable, in terminal type chmod u+x NAMEOFFILE
2018-04-23 Created 'how to' for PnP Assist scripts
2018-04-23 Fixed mistake on 'how to' for PnP assist
2018-05-04 added notes for gerbv
2018-06-08 added gerbv instructions
2018-07-20 Added back side PNP assist plugin
2018-07-20 Added footprints to makefp
2018-07-20 Created plugin versions of makefp and pnpassist.
    Updated and created How To guides
2018-07-24 pnpassist creates ./bom/ dir and puts files in it
2018-08-13 added grep command to change global labels to local
2018-08-13 pnpassist: added an import of sys libs. Not sure if this fixes anything, but seems to work on my kicad
2018-08-29 Made kicad 6 plug-in versions
2018-08-30 Updated docs to use external plugin directory
2018-09-02 Added version of pnpassist that uses System python Framework
    Also added an icon for it
2018-09-03 MakeFP: now you only have to set your lib location in the faceplate_footprint_lib.py file
    The main scripts don't need to be modified anymore to work on each machine.
2018-12-12 Tried to add stereo jack to script but it does not seem to work
2019-02-09 started 4ms-pcba-bom in boms/plugins folder - kicad bom scripts for ref
2019-02-12 made some progress on pcba script
2019-02-27 Made changes to PCBA script - added ZNotes Folder
2019-02-27 troubleshooting issue with cloning repo to windows
    this is an attempt to fix an error: 'fatal: cannot create directory - invalid argument'
    -Took quotes out of .gerbv folder name
2019-02-27 Fixed cloning issue - added windows log in Znotes for reference
2019-02-28 updated path in personal instructions
2019-02-28 added tables from work Mac into Znotes
2019-03-16 added XLR to fp script - was not successful
2019-03-21 Added script to update kicad once the nightly DMG is mounted. Script merges the new *-lib-table files with the 4ms libraries found in the existing lib-table files. Also copies the app and support fil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
2019-03-22 removed Znotes folder
2019-03-22 Fixed makefp_4_groundplane action plug-in since kicad changed the hatch enum location.
2019-04-18 moved correct file to folder
2019-04-18 updated to most recent pcba script
2019-04-24 code deletes the colon and anything before it from the fp name
    this is to get a clean name for the package type
2019-04-24 cleaned up PCBA bom folder and added proper netlist file
2019-04-24 Changed 'kicad_netlist_reader' to 'kicad_netlist_reader_4ms'
    Numeric values don't work at the start if you plan to import it it. updated PCBA bom tool to import and call upon the 4ms specific netlist reader file.
2019-04-24 need to import top and bottom information
2019-04-29 deleted 'layers' column and old '4ms-pcba-bom' file
2019-04-30 added if statement to check if 'smd' and 'points'/'totalpoints'
2019-04-30 added SMD check for more components + correct calc for totalpoints
2019-04-30 correctly removed 'layer' column
2019-05-15 script does SMD check and pin count for several components-tested on PI
2019-06-06 Updated README and plug install instructions
2019-06-06 Renamed directory for makefp kicad 6 to kicad 5.1
2019-06-06 update_kicad: change to proper directory before backing up tables
2019-06-06 picknplace_assistant: added README, removed unused files, renamed kicad 6=>5.1
2019-06-06 Removed .pyc and cache
2019-06-07 Removed compiled pyc file
2019-06-07 Igoring compiled pyc files
2019-06-13 BOM-script populates Manufacturer and Part number fields from schematic
2019-06-14 Added fork of kicad_mmccoo python scripts
2019-08-02 Added net_tools pcbnew python scripts for changing nets of zones and tracks/vias
2019-08-09 makefp: Changed py file that returns location of footprints to be a template file (in order to hide local directories)
2019-08-20 Forked update_kicad_script to cp and rsync version
2019-08-21 update_kicad script detects rsync version and uses cp or rsync appropriately (all that just to see nifty progress bars)
2019-09-16 fp script - updated encoders to all generate same hole size
    no deletes bigger cap sizes and SOC packages from back side of PCB
2019-10-03 updated underscore cleanup to include C1206 and C1210
2019-10-04 145-185: fixed decimal part_no issue and made smarter value checker
2019-10-12 pnpassist: fixed back of PCB to not be mirrored
2019-10-14 BOM: never overwrite Specs if field is not empty
2019-10-14 BOM: only prepend Value to Spec field for resistors
2019-11-06 BOM Script: fixed case sensitive error with getting manufacturer number
2019-12-09 BOM Script: Updated script to take 'designation' instead of specs
2020-02-01 Created resistor value deduction module, with unit tests
    Passes most tests, still some work to do
2020-02-01 Allowing Designation or Specifications field
    This partially reverts commit 46c000 from a month ago.
    Reason: most of our schematics use the Specifications field already, so we need to support that.
2020-02-02 BOM: group lines by Specifications, Designation, Manufacturer, and Comments
    In addition to value, footprint, and part number
2020-02-02 Bom: removed unused code and cleaned-up comments
2020-02-02 BOM: Ignore LOGO symbols in bom
2020-02-02 BOM: renamed myEqu to groupingMethod
2020-02-03 BOM: added project name and revision
2020-02-03 BOM: created get_package as a separate function
    combines package extraction from footprint name with removal of underscores. Added (limited) tests
2020-02-03 BOM: modularized deduction of Designation field with combine_specs_and_value()
2020-02-13 Put partnum magic tests in separate file
2020-02-13 Added FixMes
2020-03-30 PnpAssist: Added dialog box to select front/back/both side and destination path
2020-03-30 update_kicad: separated script for updating lib tables
2020-04-10 MKFP - Added line for 5hp in step 2
2020-08-17 Added JLCPCB ID field to BOM tool (if present)
2020-08-17 Fixed netlist reader error which choked on non A-Z 0-9 characters
2020-08-27 convertSchToNew4msLibs script: added some new resistors, removed some bad ones
2020-08-27 BOM export script which has proper headers for JLCPCB
2020-09-09 Renamed makefp dir, removed reference to Kicad 5.1
2020-09-09 Added script to convert kicad XY-pos files to JLCPCB format
2020-12-23 Added scripts to enable/disable all global libraries
2021-07-02 BOM script helper part_num_magic works with python3
2021-07-27 Make Faceplate script: kicad 6 version working better (not perfect yet)
    The GND zone does not work yet-- still figuring out the new (undocumented) kicad 6 python interface for zones
2021-07-27 Added template for faceplate_footprint_lib.py
2021-09-01 updated makefp step 3 (kicad 6)
2021-09-01 XY-pos-file-convert rotates components to match JLCPCB (WIP)
2021-10-12 XY-pos-convert: Disabled jlc_kicad_tools dependency (no Logging) (commit by Dan)
2021-10-12 Updated rotations / added rows
2021-11-04 JLCPCB pos file convert script can be run from anywhere
2021-11-09 JLCBPCB Bom generator updated to latest JLCPCB requirements
2021-12-30 Fixed BOM generator rstrip error
2022-01-04 Removed use of PCB_IO() to be compatible with Kicad6
2022-01-04 Removed PCB_IO in makefp3y
2022-03-24 remove unused stuff
2022-05-31 Added Resistor symbol generator script. Creates kicad symbol libraries using E96 values and Yageo RC series part numbers for a given resistor package (0402 to 1206), multiplier range (1Ω to 1M), and 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
2022-05-31 Moved BOM Script tests to test file
2022-05-31 Fixed tolerance showing up in Specs
2022-05-31 Added wattage, print-partnum target, lots of cleanup. Fixed 0.1% part numbers
2022-06-01 Sorted JLCPCB db by Basic/Extended so basics are chosen first
2022-06-01 Find JLCPCB IDs from db
2022-06-01 Use Ω symbol, fix db not being loaded
2022-06-01 test data to check jlc numbers
2022-06-01 Make print-bom more compatible with JLCPCB
    -use ? for JLCPCB ID if not found, prevents jlc from guessing (wrong)
    -Include CSV header, helps with importing
2022-06-06 Test BOM files for verifying JLCPCB numbers
2022-06-09 Fix README.md
2022-06-10 resistor_gen: added E24 values to match Yageo's E96+E24 product lines
2022-06-10 resistor_gen: min/max values match Yageo's datasheet per package
2022-06-10 resistor_gen: values are sorted (not split E96 then E24)
2022-06-10 resistor_gen: match JLCPCB database on exact Yageo part number
2022-06-10 resistor_gen: can print symbols with missing JLCPCB numbers
2022-06-11 More README stuff
2022-06-12 WIP: more efficiently find JLCPCB ID by yageo p/n
2022-06-12 WIP Improving 0.1% part number matching
2022-06-12 WIP: more alt partnumbers
2022-06-14 readability improvements
2022-06-14 Cleanup resistor gen help
2022-06-14 Resistor gen: fixed resistor ranges
2022-06-14 README for resistor generator
2022-06-14 README for makefp plugin
2022-06-14 makefp README updates
2022-06-15 Removed old/unused makefp scripts
2022-06-15 Added instructions to symlink makefp plugin
2022-06-15 Removed mklink instructions for Windows
2022-08-19 Fixed rounding error. Was generating some non-E96 values (40.1k instead of 40.2k)
2022-10-26 resistor_gen: Added TH resistors
2023-01-18 makefp: working for Kicad 7
2023-01-18 makefp: testing combined script
2023-01-18 make_eurorack_fp: combined script for Kicad 7
2023-01-18 makefp: consolidate steps into one plugin. Update README
2023-01-18 makefp => make_eurorack_faceplate. Consolidated Kicad 6 and 7 scripts
2023-01-18 make_eurorack_faceplate: cleanup
2023-01-28 XY-pos: Added transistor package 363 to rotation csv file
2023-01-31 Started work on posin BOM
2023-02-01 Removed deduce SMD definition and began working on posin script
2023-02-02 continued work on script
2023-02-07 Comments for BOM improvements
2023-03-03 session log 2
2023-03-09 Grouped parts into a list of dictionaries, split between production stage
2023-03-10 Dubugging groupMethod partno issue
2023-03-17 Figured out how to print to a csv row from a list of lists - now grouping by production stage
2023-03-21 BOM functions and sorts by production stage - needs to be updated with 4ms naming conventions
2023-03-22 Moved group to be furthest left column
2023-03-22 Added 0R resistor (only when tolerance is 1%)
2023-03-22 Add Yageo part number for 2010 resistors
    Comments
2023-03-22 Added Production Stage "A" to all resistors.
2023-03-22 Placed fields on a grid
2023-03-22 BOM Script: Changed stage getField from Group to Production Stage
2023-03-23 BOM Script: removed test scripts and extra unused files
2023-03-23 BOM Script: When part_no is DNP, DNP gets added to comments column
2023-03-27 resistor_gen: Add alt uniroyal part numbers
2023-03-28 BOM-script: missing Designation field
2023-03-28 BOM-script: Cleaned-up repo and renamed '4ms-pcba-bom.py' to '4ms-pcba-bom-POSIN.py'
2023-03-29 BOM-script: Added partnum_magic_test.py back to folder
2023-03-29 Bom-scripts: Removed unused and broken deduce_SMT_TH()
2023-05-22 BOM-script: if PartName differs substantially, don't group the components. Fixes grouping of parts with DNP values.
2023-06-22 MKFP Script: Added line for 'ENC_12mm_HollowShaft'
2023-06-22 MKFP: Added several IC packages to whitelist"
2023-06-22 MKFP: Added 2x5 eurorack header to white list. There may be two different spellings in library for this header
2023-06-22 MKFP: Added conversion for PB20B and LED version buttons
2023-06-22 MKFP: Added slider pot slot for Top-Up_60RFT2-B
2023-06-23 MKFP: Added MountingHole_WurthElektronik_WA-SNTI to whitelist
2024-02-13 Update resistor library template to Kicad 7.x format
2024-04-25 Update make_eurorack_fp to Kicad 8
2025-11-09 Completed voltage divider section of circuit-math.py
2025-11-11 Improved inverting op amp calculator. needs more work
2025-12-13 MKFP: Added 5mm tact switch hole and added more packages/parts to removal list
2026-06-04 WIP - updating make faceplate script to kicad 10
2026-06-04 makefp now updates copper pour
